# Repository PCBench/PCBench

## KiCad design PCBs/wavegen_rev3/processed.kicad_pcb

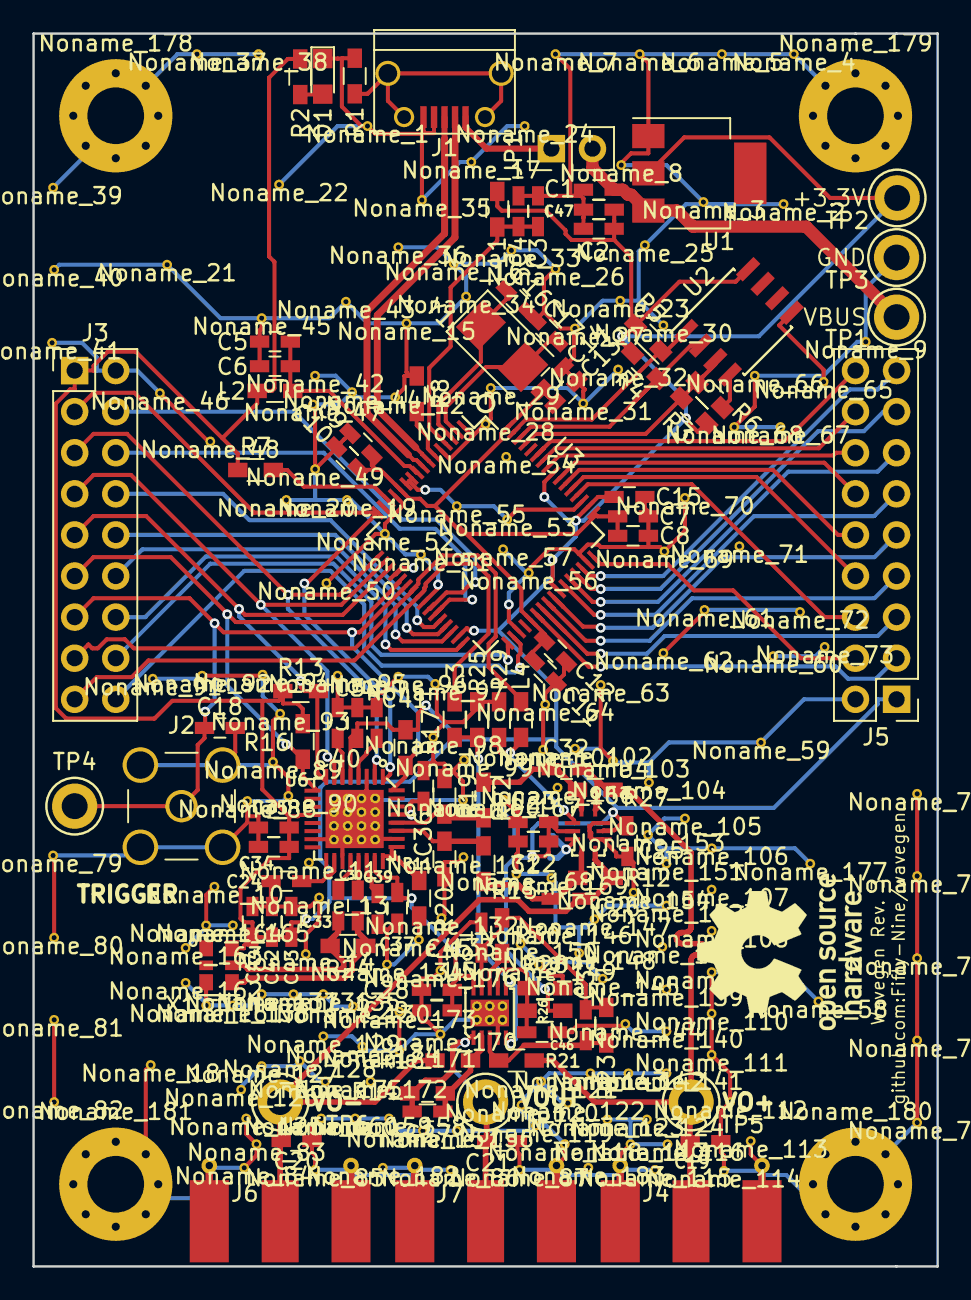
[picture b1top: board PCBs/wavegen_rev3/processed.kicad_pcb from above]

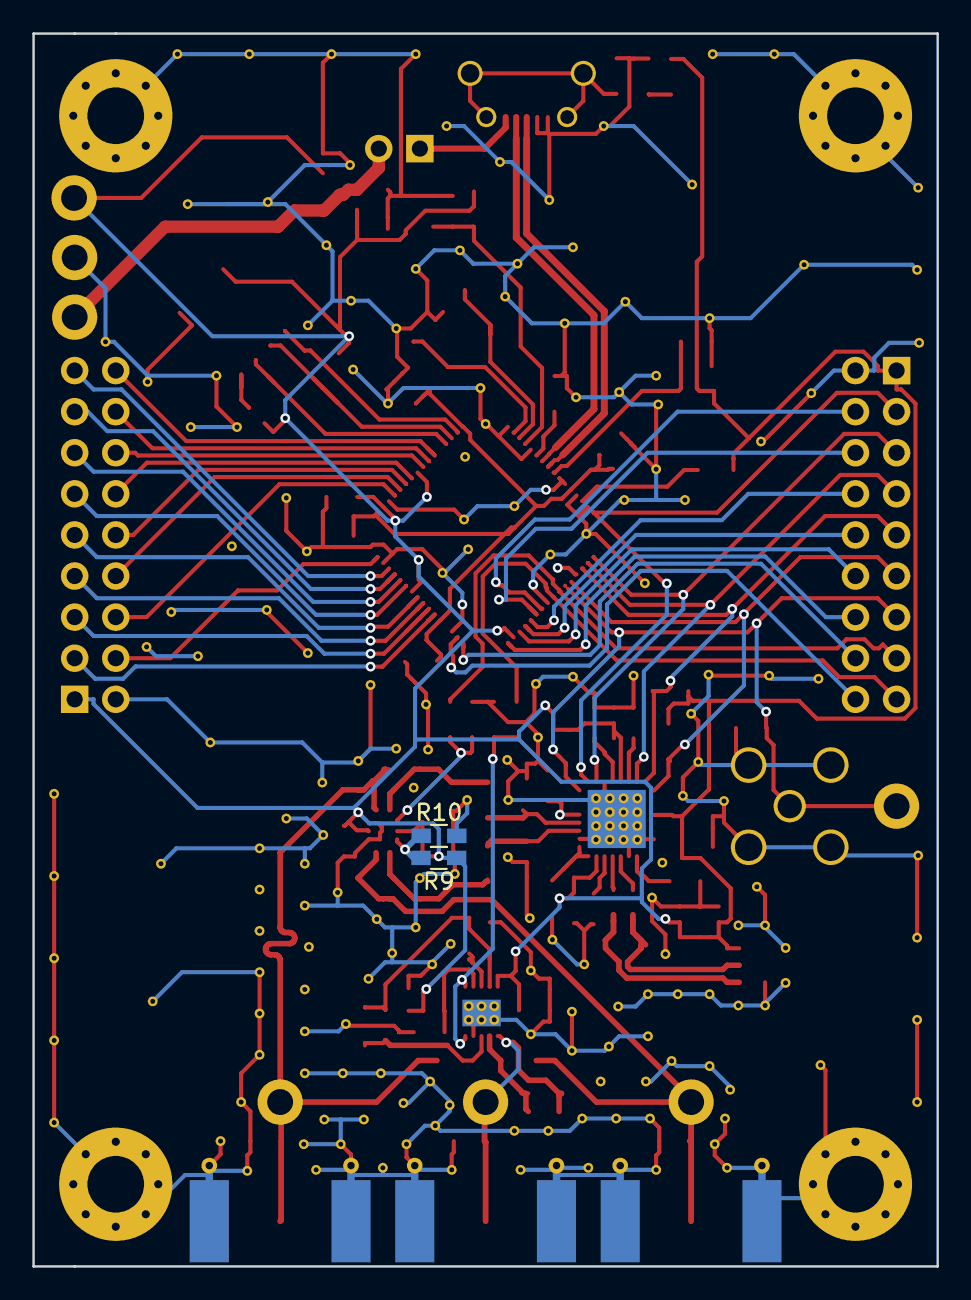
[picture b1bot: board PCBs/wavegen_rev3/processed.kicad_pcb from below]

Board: 4 copper layers, 55.9 x 76.2 mm, 288 parts (2 on the bottom side), 75 nets.

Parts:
 C19: DNP; C_0603_HandSoldering
C1, C4, C6, C8, C9, C10, C11, C12, C13, C14, C15, C23, C24, C25, C28, C30, C33, C35, C36, C37, C38, C39, C40, C41, C44, C47: 100n; C_0603_HandSoldering
C2, C22, C29, C34, C42: 10u; C_0603_HandSoldering
C3, C5, C45: 4.7u; C_0603_HandSoldering
C7: 3.3u; C_0603_HandSoldering
C16, C17: 27p; C_0603_HandSoldering
C18, C20, C21: DNP; C_0603_HandSoldering
C26, C32: 0.8p; C_0603_HandSoldering
C27, C31: 2.8p; C_0603_HandSoldering
C43, C46: 1u; C_0603_HandSoldering
D1: Green; LED_0805
J1: USB_B; USB_Micro-B-circular
J2: SMA; SMA_THT_Jack_Straight
J3, J5: CONN_02X09; Pin_Header_Straight_2x09_Pitch2.54mm
J4, J6, J7: SMA; Molex_SMA_Jack_Edge_Mount
JP1: USB_PWR; Pin_Header_Straight_1x02_Pitch2.54mm
L1, L2, L3, L4: 800m; L_0603_HandSoldering
Noname_1, Noname_2, Noname_3, Noname_4, Noname_5, Noname_6, Noname_7, Noname_8, Noname_9, Noname_10, Noname_11, Noname_12, Noname_13, Noname_14, Noname_15, Noname_16, Noname_17, Noname_18, Noname_19, Noname_20, Noname_21, Noname_22, Noname_23, Noname_24, Noname_25, Noname_26, Noname_27, Noname_28, Noname_29, Noname_30, Noname_31, Noname_32, Noname_33, Noname_34, Noname_35, Noname_36, Noname_37, Noname_38, Noname_39, Noname_40, Noname_41, Noname_42, Noname_43, Noname_44, Noname_45, Noname_46, Noname_47, Noname_48, Noname_49, Noname_50, Noname_51, Noname_52, Noname_53, Noname_54, Noname_55, Noname_56, Noname_57, Noname_58, Noname_59, Noname_60, Noname_61, Noname_62, Noname_63, Noname_64, Noname_65, Noname_66, Noname_67, Noname_68, Noname_69, Noname_70, Noname_71, Noname_72, Noname_73, Noname_74, Noname_75, Noname_76, Noname_77, Noname_78, Noname_79, Noname_80, Noname_81, Noname_82, Noname_83, Noname_84, Noname_85, Noname_86, Noname_87, Noname_88, Noname_89, Noname_90, Noname_91, Noname_92, Noname_93, Noname_94, Noname_95, Noname_96, Noname_97, Noname_98, Noname_99, Noname_100, Noname_101, Noname_102, Noname_103, Noname_104, Noname_105, Noname_106, Noname_107, Noname_108, Noname_109, Noname_110, Noname_111, Noname_112, Noname_113, Noname_114, Noname_115, Noname_116, Noname_117, Noname_118, Noname_119, Noname_120, Noname_121, Noname_122, Noname_123, Noname_124, Noname_125, Noname_126, Noname_127, Noname_128, Noname_129, Noname_130, Noname_131, Noname_132, Noname_133, Noname_134, Noname_135, Noname_136, Noname_137, Noname_138, Noname_139, Noname_140, Noname_141, Noname_142, Noname_143, Noname_144, Noname_145, Noname_146, Noname_147, Noname_148, Noname_149, Noname_150, Noname_151, Noname_152, Noname_153, Noname_154, Noname_155, Noname_156, Noname_157, Noname_158, Noname_159, Noname_160, Noname_161, Noname_162, Noname_163, Noname_164, Noname_165, Noname_166, Noname_167, Noname_168, Noname_169, Noname_170, Noname_171, Noname_172, Noname_173, Noname_174, Noname_175, Noname_176, Noname_177, Noname_182, Noname_183: ManualVia
Noname_178, Noname_179, Noname_180, Noname_181: MountingHole_3.5mm_Pad_Via
R1, R9, R10: DNP; R_0603_HandSoldering
R2: 500; R_0603_HandSoldering
R3, R4, R5: 10k; R_0603_HandSoldering
R6: 2.2k; R_0603_HandSoldering
R7, R13, R16, R17, R25, R29: 4.7k; R_0603_HandSoldering
R8: 12k; R_0603_HandSoldering
R11: 8.25k; R_0603_HandSoldering
R12, R27: 510; R_0603_HandSoldering
R14, R23: 1.5k; R_0603_HandSoldering
R15, R19, R20, R22, R24: 100; R_0603_HandSoldering
R18, R21: 1k; R_0603_HandSoldering
R26, R28: 36k; R_0603_HandSoldering
R30: 18k; R_0603_HandSoldering
TP1: VBUS; Test_Point_Keystone_5005-5009_Compact
TP2: +3.3V; Test_Point_Keystone_5005-5009_Compact
TP3: GND; Test_Point_Keystone_5005-5009_Compact
TP4: TRIGGER; Test_Point_Keystone_5005-5009_Compact
TP5: VOUT+; Test_Point_Keystone_5005-5009_Compact
TP6: VOUT-; Test_Point_Keystone_5005-5009_Compact
TP7: VOUT; Test_Point_Keystone_5005-5009_Compact
U1: LD1117S33TR; SOT-223
U2: 93LCxxB; SOIC-8_3.9x4.9mm_Pitch1.27mm
U3: FT2232H; LQFP-64_10x10mm_Pitch0.5mm
U4: LTC6409; LTC6409-UDB
U5: LTC6269; LTC6269-10DFN
U6: AD9102; AD9102-10LFCSP
X1: DSC1123; 3225XO
Y1: 12MHz; Crystal_SMD_5032-2pin_5.0x3.2mm

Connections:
+3V3: C2.1, C15.1, C22.1, C23.1, C25.1, C28.1, C29.1, C34.2, C35.2, C36.2, C37.1, C38.1, C42.1, C43.1, C44.1, C47.1, J3.1, J5.1, L1.1, L2.1, R2.1, R3.1, R4.1, R5.1, R7.1, R9.1, R13.1, R16.1, R17.1, R26.1, TP2.1, U1.2, U2.8, U3.20, U3.31, U3.42, U3.50, U3.56, U4.4, U4.9, U5.10, U6.5, U6.12, U6.23, U6.29, X1.6
/Analog/+1.65V: C31.1, C45.1, R23.2, R30.2, U5.9
/Connectors/ACBUS0: J3.4, U3.26
/Connectors/ACBUS1: J3.6, U3.27
/Connectors/ACBUS2: J3.8, U3.28
/Connectors/ACBUS3: J3.10, U3.29
/Connectors/ACBUS4: J3.12, U3.30
/Connectors/ACBUS5: J3.14, U3.32
/Connectors/ACBUS6: J3.16, U3.33
/Connectors/ACBUS7: J3.18, U3.34
/Connectors/BCBUS0: J5.4, U3.48
/Connectors/BCBUS1: J5.6, U3.52
/Connectors/BCBUS2: J5.8, U3.53
/Connectors/BCBUS3: J5.10, U3.54
/Connectors/BCBUS4: J5.12, U3.55
/Connectors/BCBUS5: J5.14, U3.57
/Connectors/BCBUS6: J5.16, U3.58
/Connectors/BCBUS7: J5.18, U3.59
/Connectors/BDBUS0: J5.3, U3.38
/Connectors/BDBUS1: J5.5, U3.39
/Connectors/BDBUS2: J5.7, U3.40
/Connectors/BDBUS3: J5.9, U3.41
/Connectors/BDBUS4: J5.11, U3.43
/Connectors/BDBUS5: J5.13, U3.44
/Connectors/BDBUS6: J5.15, U3.45
/Connectors/BDBUS7: J5.17, U3.46
/FTDI/REF: R8.2, U3.6
/FTDI/VREGOUT: C7.1, C8.1, C9.1, C10.1, C11.1, C12.1, C13.1, C14.1, U3.12, U3.37, U3.49, U3.64
/FTDI/nRESET: R7.2, U3.14
AMP0_EN: J3.15, L4.1, U3.23
AMP1_EN: J3.17, L3.2, U3.24
DCLK+: C30.2, R24.1, X1.4
DCLK-: C33.2, R24.2, X1.5
FTEECLK: R4.2, U2.2, U3.62
FTEECS: R5.2, U2.1, U3.63
FTEEDATA: R3.2, R6.1, U2.3, U3.61
FTOSC+: C16.1, U3.3, Y1.1
FTOSC-: C17.1, U3.2, Y1.2
FTVPHY: C3.1, C4.1, L1.2, U3.4
FTVPLL: C5.1, C6.1, L2.2, U3.9
GNDA: C19.1, C1.2, C2.2, C3.2, C4.2, C5.2, C6.2, C7.2, C8.2, C9.2, C10.2, C11.2, C12.2, C13.2, C14.2, C15.2, C16.2, C17.2, C18.1, C20.1, C21.1, C22.2, C23.2, C24.1, C25.2, C28.2, C29.2, C34.1, C35.1, C36.1, C37.2, C38.2, C39.2, C40.2, C41.2, C42.2, C43.2, C44.2, C45.2, C46.2, C47.2, D1.1, J1.4, J2.2, J3.2, J4.2, J5.2, J6.2, J7.2, Noname_178.1, Noname_179.1, Noname_180.1, Noname_181.1, R1.1, R8.1, R10.2, R11.1, R19.1, R20.1, R25.2, R28.2, R29.2, TP3.1, U1.1, U2.5, U3.1, U3.5, U3.10, U3.11, U3.13, U3.15, U3.25, U3.35, U3.47, U3.51, U4.8, U4.10, U4.11, U5.4, U5.11, U6.3, U6.15, U6.19, U6.26, U6.EP, X1.3
unnamed: C1.1, JP1.2, TP1.1, U1.3
unnamed: C24.2, U6.18
unnamed: C26.2, R12.1, R15.2, U4.6
unnamed: C27.1, R14.2, R18.2, U5.2
unnamed: C30.1, U6.21
unnamed: C31.2, R21.2, R23.1, U5.3
unnamed: C32.2, R22.2, R27.1, U4.2
unnamed: C33.1, U6.20
unnamed: C39.1, U6.22
unnamed: C40.1, U6.6
unnamed: C41.1, U6.4
unnamed: C46.1, R26.2, R28.1, U5.7
unnamed: D1.2, R2.2
unnamed: J1.1, JP1.1
unnamed: J1.5, R1.2
unnamed: L3.1, R25.1, U5.5, U5.6
unnamed: L4.2, R29.1, U4.3
unnamed: R6.2, U2.4
unnamed: R11.2, U6.24, U6.25
unnamed: R15.1, R20.2, U6.27
unnamed: R19.2, R22.1, U6.28
unnamed: R30.1, U5.8
RESET: J3.11, R16.2, U3.21, U6.9
SPI_CLK: J3.3, U3.16, U6.1
SPI_CS: J3.9, R13.2, U3.19, U6.8
SPI_DI: J3.7, U3.18, U6.7
SPI_DO: J3.5, U3.17, U6.2
TRIGGER: C18.2, J2.1, J3.13, R17.2, TP4.1, U3.22, U6.32
USB_D+: J1.3, U3.8
USB_D-: J1.2, U3.7
VOCM: R9.2, R10.1, U4.5
VOUT: C21.2, C27.2, J7.1, R14.1, TP7.1, U5.1
VOUT+: C19.2, C32.1, J4.1, R21.1, R27.2, TP5.1, U4.1
VOUT-: C20.2, C26.1, J6.1, R12.2, R18.1, TP6.1, U4.7

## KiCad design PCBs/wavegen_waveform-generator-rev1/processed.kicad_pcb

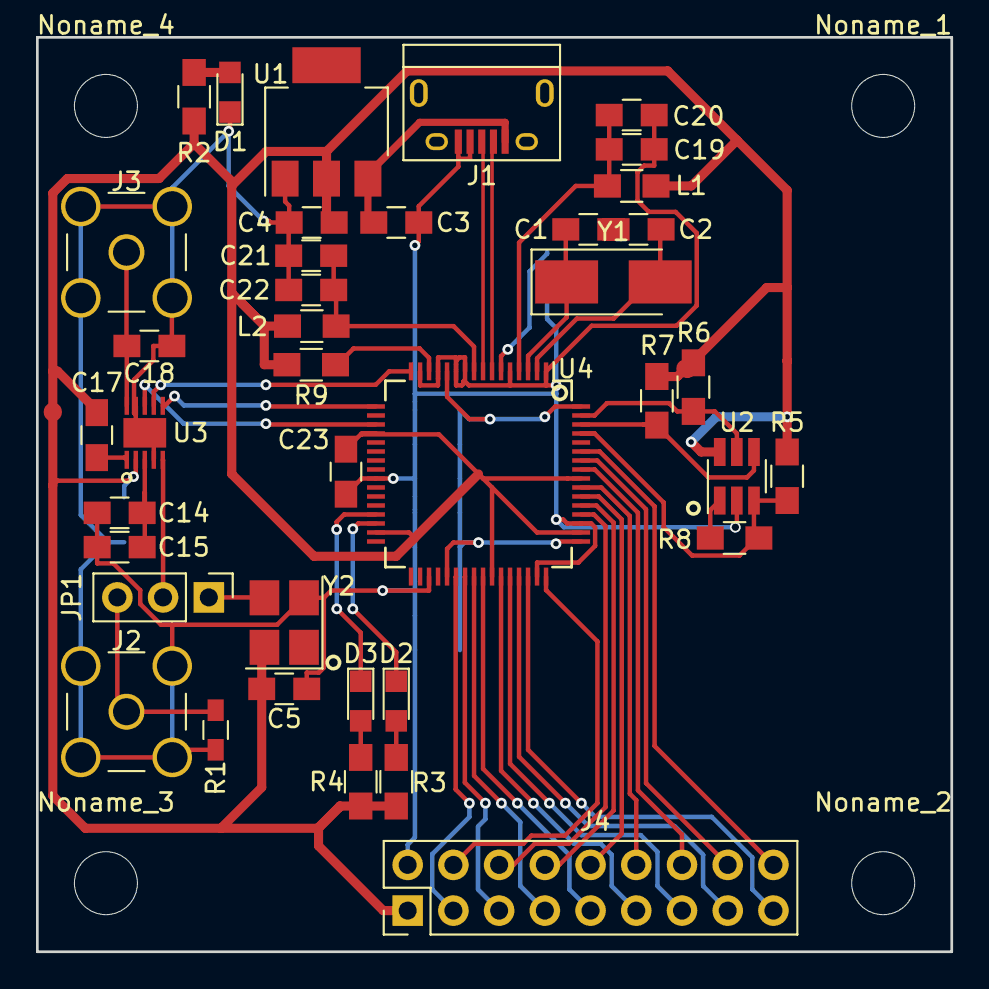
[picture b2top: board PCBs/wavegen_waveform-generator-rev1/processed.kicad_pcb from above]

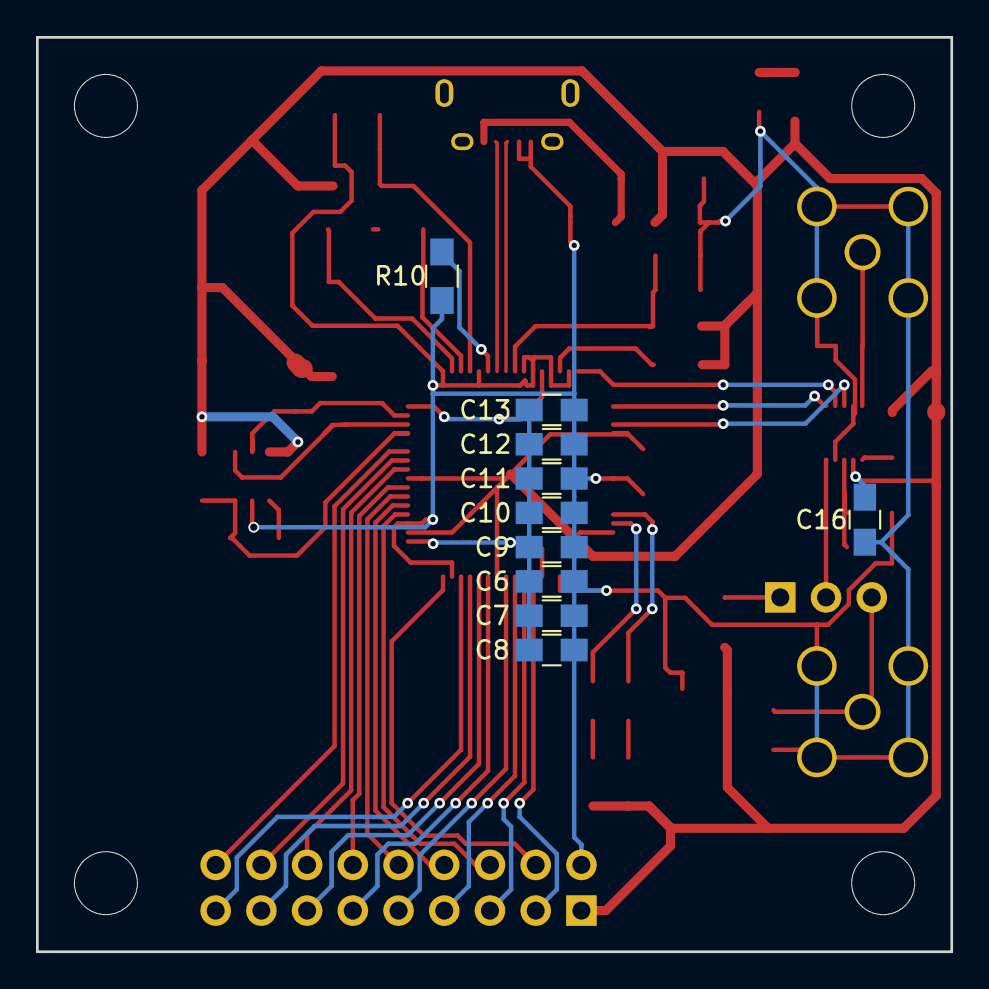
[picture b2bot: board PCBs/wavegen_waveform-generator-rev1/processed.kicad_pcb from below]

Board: 2 copper layers, 50.8 x 50.8 mm, 53 parts (10 on the bottom side), 47 nets.

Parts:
C1, C2: 27p; C_0805_HandSoldering
C3, C5, C7, C8, C9, C10, C11, C12, C13, C14, C16, C18, C20, C22, C23: 100n; C_0805_HandSoldering
C4, C15: 10u; C_0805_HandSoldering
C6: 3.3u; C_0805_HandSoldering
C17: 10n; C_0805_HandSoldering
C19, C21: 4.7u; C_0805_HandSoldering
D1, D2, D3: LED_Small; LED_0805
J1: USB_B; USB_Micro-B
J2: EXT_CLK; SMA_THT_Jack_Straight
J3: VOUT; SMA_THT_Jack_Straight
J4: CONN_02X09; Pin_Header_Straight_2x09_Pitch2.54mm
JP1: CLK_SELECT; Pin_Header_Straight_1x03_Pitch2.54mm
L1, L2: 800m; L_0805_HandSoldering
Noname_1, Noname_2, Noname_3, Noname_4: MountingHole_3.5mm
R1: 50; R_0603_HandSoldering
R2, R3, R4: 470; R_0805_HandSoldering
R5, R6, R7: 10k; R_0805_HandSoldering
R8: 2.2k; R_0805_HandSoldering
R9: 1k; R_0805_HandSoldering
R10: 12k; R_0805_HandSoldering
U1: LD1117S33TR; SOT-223
U2: 93LC46BT; SOT-23-6_Handsoldering
U3: AD9837
U4: FT2232H; LQFP-64_10x10mm_Pitch0.5mm
Y1: 12MHz; Crystal_SMD_5032-2pin_5.0x3.2mm_HandSoldering
Y2: OXETGCJANF; Oscillator_SMD_Abracon_ASE-4pin_3.2x2.5mm_HandSoldering

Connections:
+3V3: C4.1, C5.1, C16.1, C17.1, C23.1, J4.1, L1.1, L2.1, R2.2, R3.2, R4.2, R5.1, R6.1, R7.1, R9.2, U1.2, U2.6, U3.2, U4.20, U4.31, U4.42, U4.50, U4.56, Y2.4
DAC_CLK: JP1.2, U3.5
EECLK: R7.2, U2.4, U4.62
EECS: R6.2, U2.5, U4.63
EEDATA: R5.2, R8.1, U2.3, U4.61
FTOSCI: C2.1, U4.2, Y1.2
FTOSCO: C1.1, U4.3, Y1.1
FTRXLED: D3.1, U4.29
FTTXLED: D2.1, U4.30
FTVPHY: C19.1, C20.1, L1.2, U4.4
FTVPLL: C21.1, C22.1, L2.2, U4.9
GNDA: C3.2, C4.2, C5.2, C6.2, C7.2, C8.2, C9.2, C10.2, C11.2, C12.2, C13.2, C14.2, C15.2, C16.2, C18.2, C19.2, C20.2, C21.2, C22.2, C23.2, D1.1, J1.4, J1.5, J2.2, J3.2, J4.2, R1.2, R10.2, U1.1, U2.2, U3.4, U3.9, U3.11, U4.1, U4.5, U4.10, U4.11, U4.13, U4.15, U4.25, U4.35, U4.47, U4.51, Y2.2
unnamed: C1.2, C2.2
unnamed: C3.1, J1.1, U1.3
unnamed: C6.1, C7.1, C8.1, C9.1, C10.1, C11.1, C12.1, C13.1, U4.12, U4.37, U4.49, U4.64
unnamed: C14.1, C15.1, U3.3
unnamed: C17.2, U3.1
unnamed: C18.1, J3.1, U3.10
unnamed: D1.2, R2.1
unnamed: D2.2, R3.1
unnamed: D3.2, R4.1
unnamed: J2.1, JP1.3, R1.1
unnamed: J4.3, U4.38
unnamed: J4.4, U4.48
unnamed: J4.5, U4.39
unnamed: J4.6, U4.52
unnamed: J4.7, U4.40
unnamed: J4.8, U4.53
unnamed: J4.9, U4.41
unnamed: J4.10, U4.54
unnamed: J4.11, U4.43
unnamed: J4.12, U4.55
unnamed: J4.13, U4.44
unnamed: J4.14, U4.57
unnamed: J4.15, U4.45
unnamed: J4.16, U4.58
unnamed: J4.17, U4.46
unnamed: J4.18, U4.59
unnamed: JP1.1, Y2.3
unnamed: R8.2, U2.1
unnamed: R9.1, U4.14
unnamed: R10.1, U4.6
unnamed: U3.6, U4.17
unnamed: U3.7, U4.16
unnamed: U3.8, U4.19
USB_D+: J1.3, U4.8
USB_D-: J1.2, U4.7
